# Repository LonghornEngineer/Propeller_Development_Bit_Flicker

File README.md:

# Propeller_Development_Bit_Flicker

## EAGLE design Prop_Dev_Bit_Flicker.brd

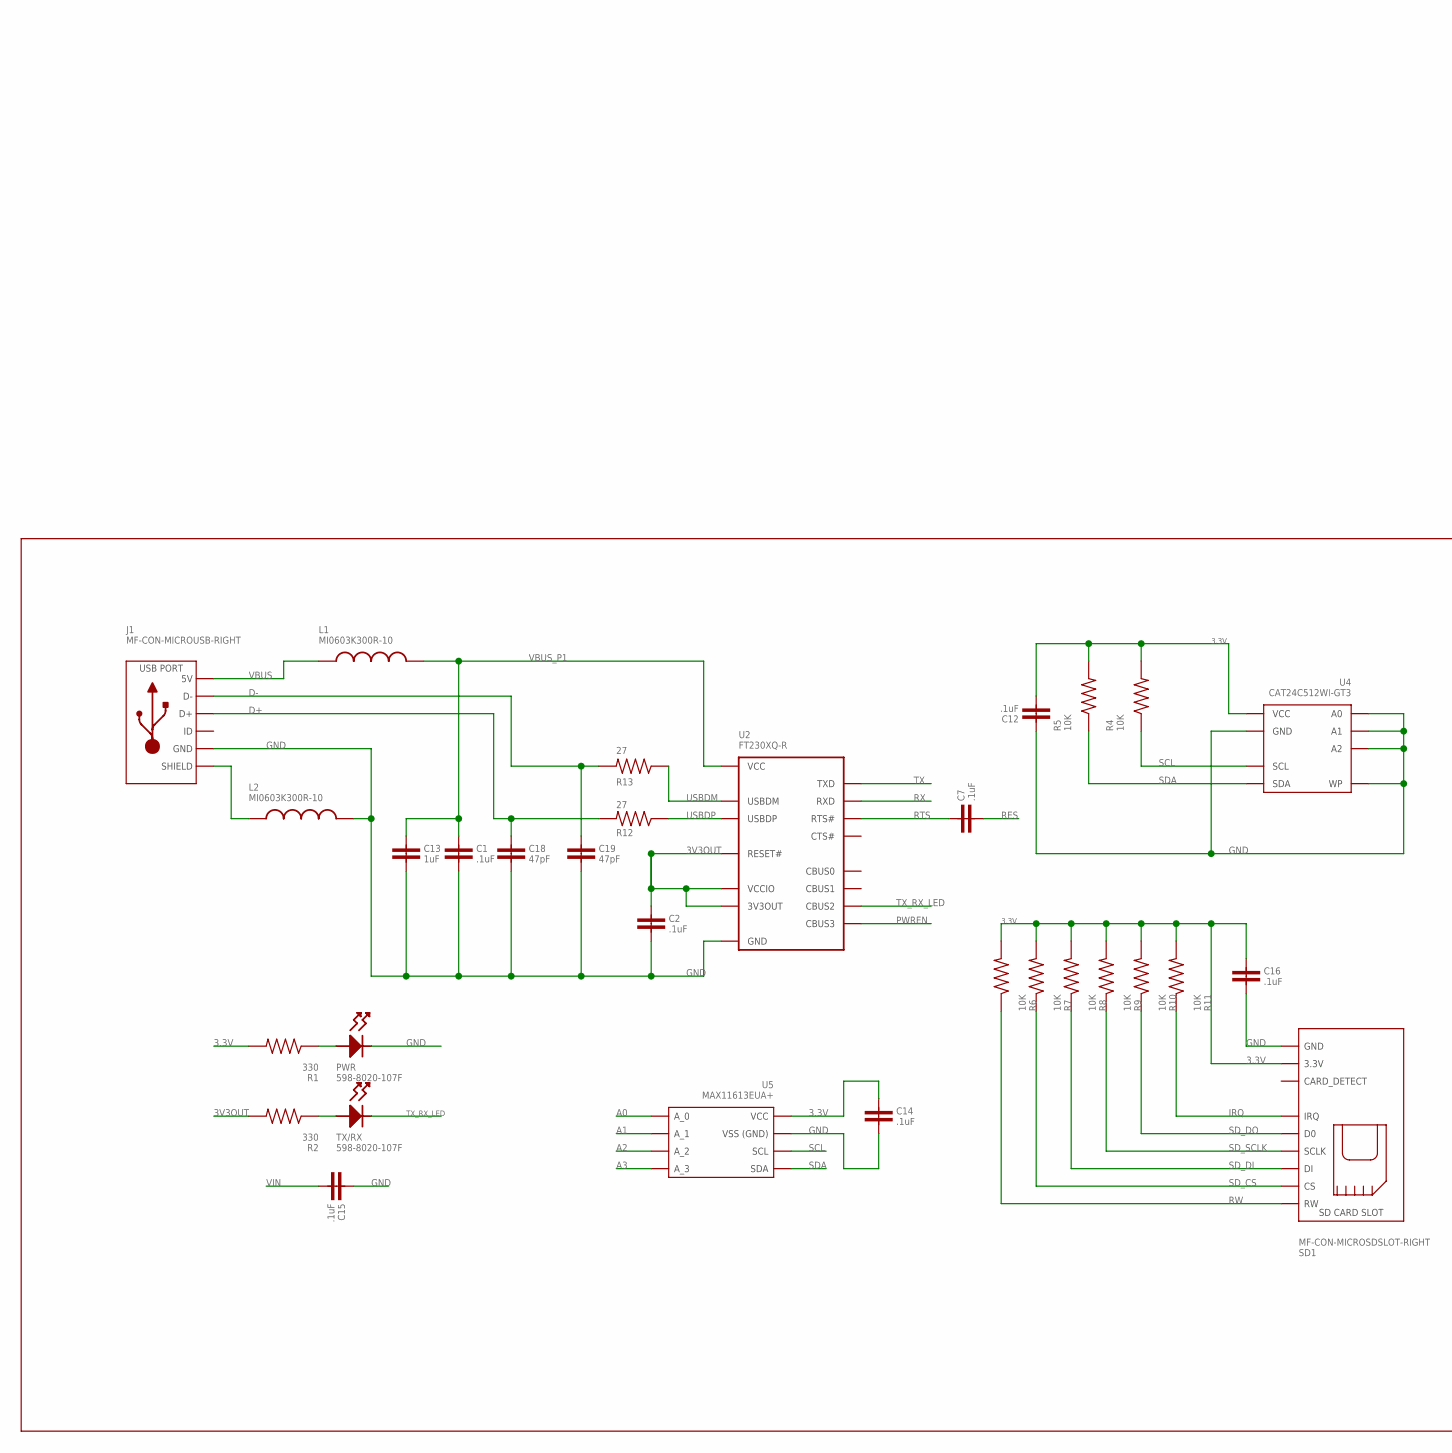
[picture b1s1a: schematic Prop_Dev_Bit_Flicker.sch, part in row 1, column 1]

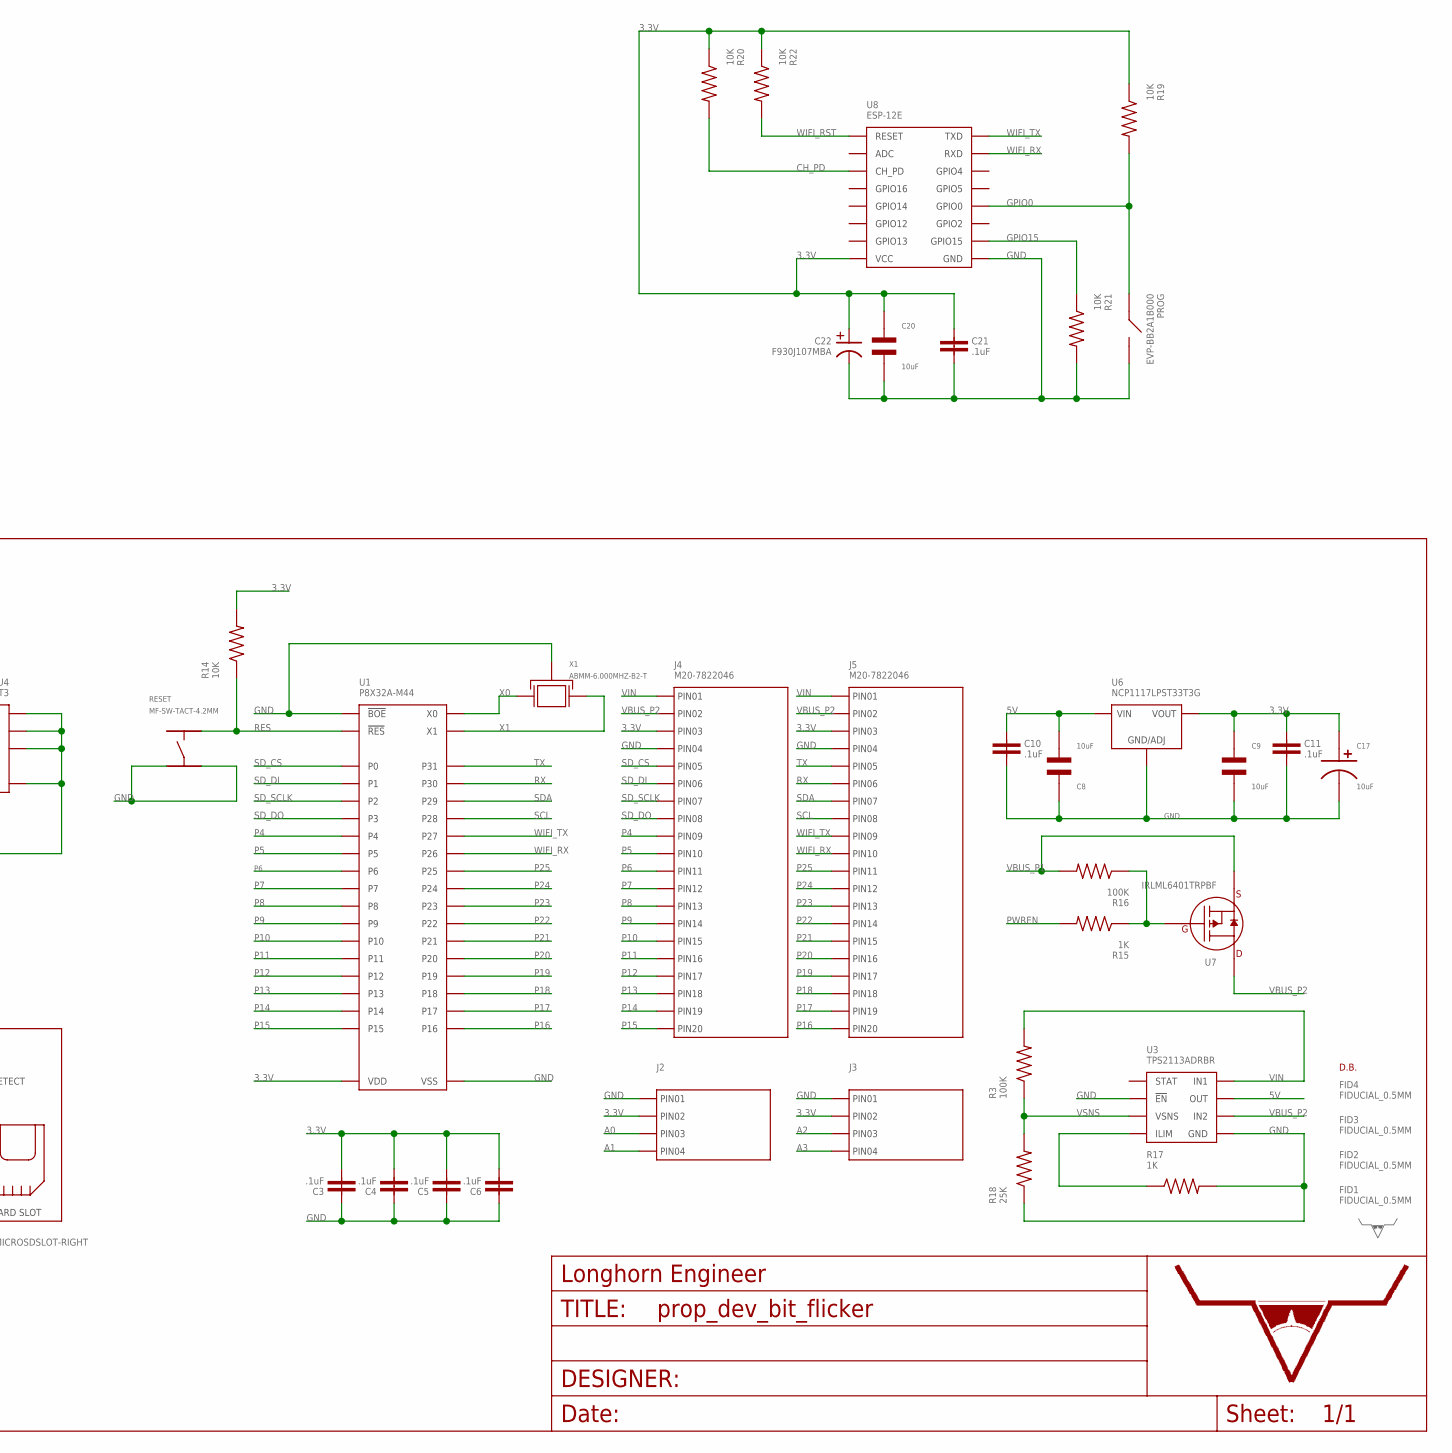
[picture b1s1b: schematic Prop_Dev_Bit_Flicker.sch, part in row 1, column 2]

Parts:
C1, C2, C3, C4, C5, C6, C7, C10, C11, C12, C14, C15, C16, C21: .1uF; 0603
C8, C9, C20: 10uF; C1206
C13: 1uF; 0603
C17: 10uF; CP4MM
C18, C19: 47pF; 0603
C22: F930J107MBA; CASE_B
FID1, FID2, FID3, FID4: FIDUCIAL_0.5MM
J1: MF-CON-MICROUSB-RIGHT; MICROUSB-RIGHT
J2, J3: CON_01X04_2.54MM_PIN_HEADER; 2.54MM_01X04_PIN_HEADER
J4, J5: M20-7822046; 2.54MM_01X20_PIN_HEADER
L1, L2: MI0603K300R-10; 0603
PROG: EVP-BB2A1B000; EVPBB
PWR: 598-8020-107F; LED_0805
R1, R2: 330; 0603
R3, R16: 100K; 0603
R4, R5, R6, R7, R8, R9, R10, R11, R14, R19, R20, R21, R22: 10K; 0603
R12, R13: 27; 0603
R15, R17: 1K; 0603
R18: 25K; 0603
RESET: MF-SW-TACT-4.2MM; TACT4.2MM
SD1: MF-CON-MICROSDSLOT-RIGHT; MICROSDSLOT-RIGHT
TX/RX: 598-8020-107F; LED_0805
U1: P8X32A-M44; P8X32A_QFN-44
U2: FT230XQ-R; FT230X_QFN-16
U3: TPS2113ADRBR; TPS211X_SON-8
U4: CAT24C512WI-GT3; SOIC-8_W
U5: MAX11613EUA+; MAX11613_UMAX-8
U6: NCP1117LPST33T3G; SOT-223-3
U7: IRLML6401TRPBF; SOT-23-3
U8: ESP-12E
U$1: LHE_FRAME
U$2: LHE_LOGOLHE_LOGO; LHE_LOGO
U$3: DB_LOGO_SILK_SMALL; DB_SILK_SMALL
X1: ABMM-6.000MHZ-B2-T; 7MMX5MM

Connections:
3.3V: C3.2, C4.2, C5.2, C6.2, C9.P$1, C11.1, C12.2, C14.1, C16.1, C17.P$1, C20.P$1, C21.1, C22.P (POS), J2.2, J3.2, J4.3, J5.3, R1.2, R4.2, R5.2, R6.2, R7.2, R8.2, R9.2, R10.2, R11.2, R14.2, R19.1, R20.1, R22.1, SD1.PIN4 (3.3V), U1.8 (VDD), U1.18 (VDD), U1.30 (VDD), U1.40 (VDD), U4.8 (VCC), U5.P$8 (VCC), U6.P$1 (VOUT), U6.P$3 (VOUT), U8.P$8 (VCC)
3V3OUT: C2.1, R2.2, U2.1 (VCCIO), U2.8 (3V3OUT), U2.9 (RESET#)
5V: C8.P$2, C10.1, U3.7 (OUT), U6.P$4 (VIN)
A0: J2.3, U5.P$1 (A_0)
A1: J2.4, U5.P$2 (A_1)
A2: J3.3, U5.P$3 (A_2)
A3: J3.4, U5.P$4 (A_3)
CH_PD: R20.2, U8.P$3 (CH_PD)
D+: C18.1, J1.3 (D+), R12.2
D-: C19.1, J1.2 (D-), R13.2
GND: C1.2, C2.2, C3.1, C4.1, C5.1, C6.1, C8.P$1, C9.P$2, C10.2, C11.2, C12.1, C13.2, C14.2, C15.1, C16.2, C17.P$2, C18.2, C19.2, C20.P$2, C21.2, C22.N (NEG), J1.5 (GND), J2.1, J3.1, J4.4, J5.4, L2.2, PROG.P$3 (B), PROG.P$4 (B), PWR.CATHODE, R17.2, R18.1, R21.2, RESET.P$3, RESET.P$4, SD1.G0 (GND), SD1.G1 (GND), SD1.PIN6 (GND), U1.5 (VSS), U1.6 (!BOE), U1.17 (VSS), U1.27 (VSS), U1.39 (VSS), U2.3 (GND), U2.13 (GND), U2.PAD (GND), U3.2 (!EN), U3.5 (GND), U3.PAD (GND), U4.1 (A0), U4.2 (A1), U4.3 (A2), U4.4 (GND), U4.7 (WP), U5.P$7 (GND), U6.P$2 (GND/ADJ), U8.P$15 (GND), X1.P$2 (GND), X1.P$4 (GND)
GPIO0: PROG.P$1 (A), PROG.P$2 (A), R19.2, U8.P$18 (GPIO0)
GPIO15: R21.1, U8.P$16 (GPIO15)
IRQ: R11.1, SD1.PIN8 (IRQ)
unnamed: PWR.ANODE, R1.1
unnamed: R2.1, TX/RX.ANODE
unnamed: J1.S1 (SLD), J1.S2 (SLD), J1.S3 (SLD), J1.S4 (SLD), J1.S5 (SLD), J1.S6 (SLD), L2.1
unnamed: R17.1, U3.4 (ILIM)
unnamed: R15.1, R16.1, U7.1 (GATE)
P4: J4.9, U1.1 (P4)
P5: J4.10, U1.2 (P5)
P6: J4.11, U1.3 (P6)
P7: J4.12, U1.4 (P7)
P8: J4.13, U1.9 (P8)
P9: J4.14, U1.10 (P9)
P10: J4.15, U1.11 (P10)
P11: J4.16, U1.12 (P11)
P12: J4.17, U1.13 (P12)
P13: J4.18, U1.14 (P13)
P14: J4.19, U1.15 (P14)
P15: J4.20, U1.16 (P15)
P16: J5.20, U1.19 (P16)
P17: J5.19, U1.20 (P17)
P18: J5.18, U1.21 (P18)
P19: J5.17, U1.22 (P19)
P20: J5.16, U1.23 (P20)
P21: J5.15, U1.24 (P21)
P22: J5.14, U1.25 (P22)
P23: J5.13, U1.26 (P23)
P24: J5.12, U1.31 (P24)
P25: J5.11, U1.32 (P25)
PWREN: R15.2, U2.14 (CBUS3)
RES: C7.2, R14.1, RESET.P$2, U1.7 (!RES)
RTS: C7.1, U2.16 (RTS#)
RW: R6.1, SD1.PIN1 (RW)
RX: J5.6, U1.37 (P30), U2.2 (RXD)
SCL: J5.8, R4.1, U1.35 (P28), U4.6 (SCL), U5.P$5 (SCL)
SDA: J5.7, R5.1, U1.36 (P29), U4.5 (SDA), U5.P$6 (SDA)
SD_CS: J4.5, R7.1, SD1.PIN2 (CS), U1.41 (P0)
SD_DI: J4.6, R8.1, SD1.PIN3 (DI), U1.42 (P1)
SD_DO: J4.8, R10.1, SD1.PIN7 (D0), U1.44 (P3)
SD_SCLK: J4.7, R9.1, SD1.PIN5 (SCLK), U1.43 (P2)
TX: J5.5, U1.38 (P31), U2.15 (TXD)
TX_RX_LED: TX/RX.CATHODE, U2.5 (CBUS2)
USBDM: R13.1, U2.7 (USBDM)
USBDP: R12.1, U2.6 (USBDP)
VBUS: J1.1 (5V), L1.1
VBUS_P1: C1.1, C13.1, L1.2, R16.2, U2.10 (VCC), U7.2 (SOURCE)
VBUS_P2: J4.2, J5.2, U3.6 (IN2), U7.3 (DRAIN)
VIN: C15.2, J4.1, J5.1, R3.2, U3.8 (IN1)
VSNS: R3.1, R18.2, U3.3 (VSNS)
WIFI_RST: R22.2, U8.P$1 (RESET)
WIFI_RX: J5.10, U1.33 (P26), U8.P$21 (RXD)
WIFI_TX: J5.9, U1.34 (P27), U8.P$22 (TXD)
X0: U1.29 (X0), X1.P$3 (X1)
X1: U1.28 (X1), X1.P$1 (X0)

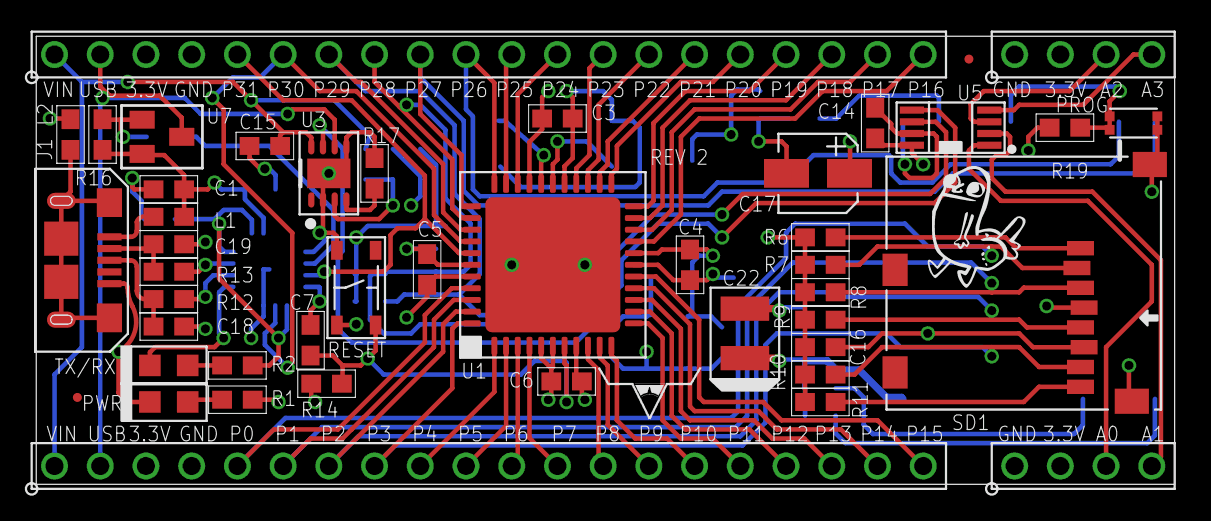
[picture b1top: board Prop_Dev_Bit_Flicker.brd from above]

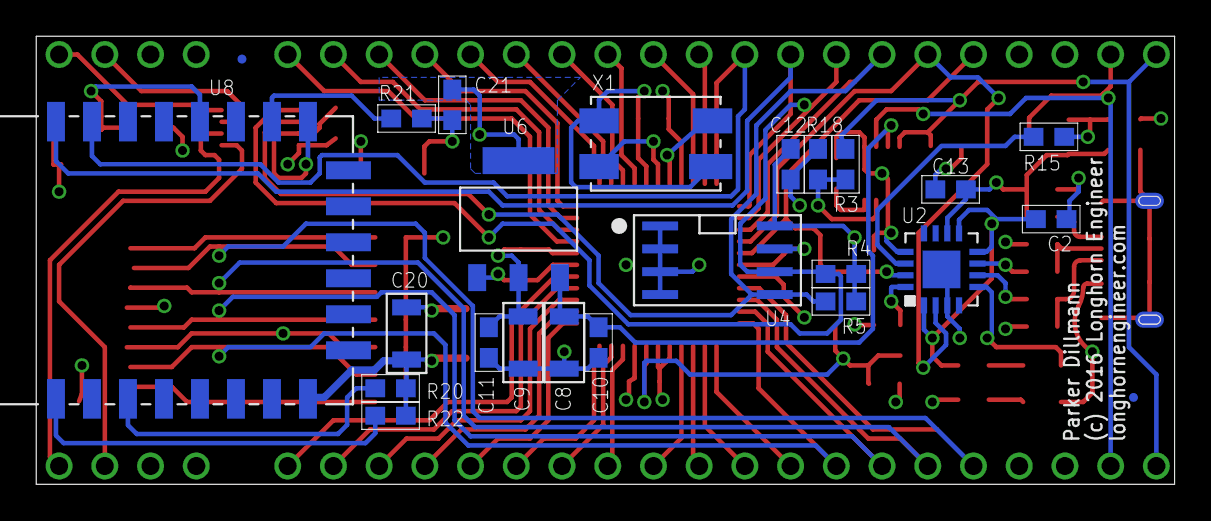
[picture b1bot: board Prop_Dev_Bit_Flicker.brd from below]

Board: 4 copper layers, 63.2 x 24.9 mm, 72 parts (25 on the bottom side), 66 nets.

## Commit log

2016-03-22 First push of files. Schematic Finalized.
2016-03-29 Working on layout.
2016-04-01 preliminary layout complete.
2016-04-02 top done. bottom next on silkscreen and trace clean u
2016-04-04 Finished REV 2. Added Fids.
2016-04-05 Added DB
2016-04-05 Switch added to GPIO0 for the ESP-12E for flashing.
2016-04-26 Fixed EP-12E and new camfiles.
2016-04-26 Fixed part number for Prop to P8X32A-M44
2016-04-27 Fixed FT230X template.
2016-04-28 New Camfiles and added Tant Cap 100uF to 3.3V
2016-04-28 Fixed silkscreen on top. Moved LHE Logo.

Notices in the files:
parts and their libraries:
PP_Aesthetics: (c) 2016 Longhorn Engineer
